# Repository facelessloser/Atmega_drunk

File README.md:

Atmega_drunk
============

Breathalyser build around the atmega328 with a OLED screen and a MQ-3 alcohol sensor

You will need the Adafruit OLED screen library. You can download them from here - https://github.com/adafruit/Adafruit_SSD1306

Also you will need the grafix library. You can download them from here - https://github.com/adafruit/Adafruit-GFX-Library

Blog post can be found here 

https://facelesstech.wordpress.com/2015/02/07/lets-get-atmega_drunk/

video can be found here

http://youtu.be/ZPd7yIUckZc

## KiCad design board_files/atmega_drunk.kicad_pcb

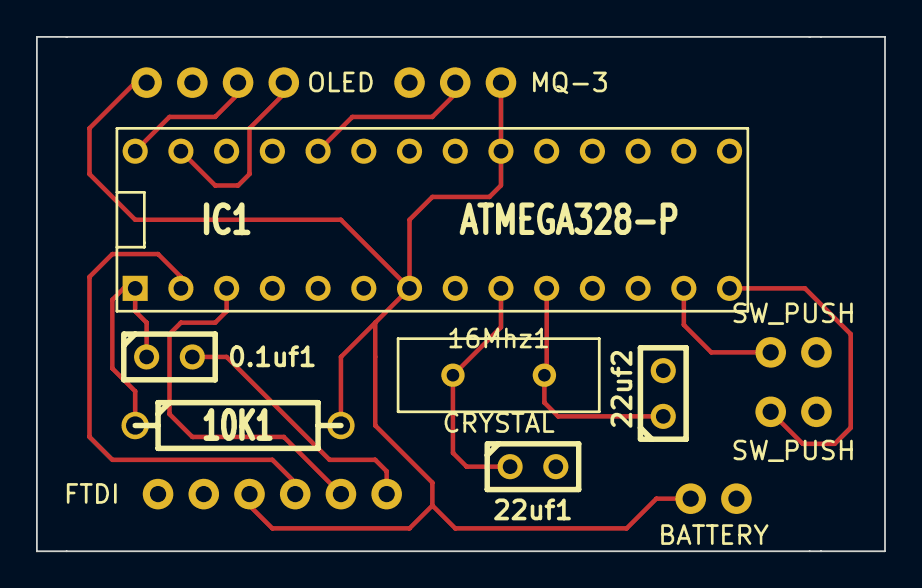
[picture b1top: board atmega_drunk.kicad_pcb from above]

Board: 2 copper layers, 47.1 x 28.6 mm, 13 parts (0 on the bottom side), 13 nets.

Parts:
0.1uf1, 22uf1, 22uf2: C; C1
10K1: R; R4-5
16Mhz1: CRYSTAL; Crystal_custom
BT1: BATTERY; Battery_headers
IC1: ATMEGA328-P; DIP_28_300_SOCKET
SW2: SW_PUSH; PUSH_BUTTONS_CUSTOM
U1: MQ-3
U2: FTDI
U3: OLED; OLED_HEADER
VAL: REF; OSH
eeSW3: SW_PUSH; PUSH_BUTTONS_CUSTOM

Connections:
GND: 22uf1.2, 22uf2.2, BT1.2, IC1.8, IC1.22, SW2.2, U1.1, U2.6, U3.2, eeSW3.2
unnamed: IC1.24, U1.2
unnamed: 0.1uf1.1, 10K1.1, IC1.1
unnamed: IC1.3, U2.2
unnamed: IC1.2, U2.3
unnamed: IC1.27, U3.4
unnamed: IC1.13, SW2.1
unnamed: IC1.14, eeSW3.1
unnamed: IC1.28, U3.3
unnamed: 16Mhz1.1, 22uf2.1, IC1.10
unnamed: 16Mhz1.2, 22uf1.1, IC1.9
unnamed: 0.1uf1.2, U2.1
VCC: 10K1.2, BT1.1, IC1.7, IC1.20, U1.3, U2.4, U3.1

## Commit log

2014-12-21 Gurber files to make atmega_drunk
2015-01-12 atmege drunk schematics and breakboard layout
2015-01-13 added links to the OLED librarys
2015-01-13 Arduino files
2015-01-31 changed the font to be bigger size
2015-02-01 changed font size and wrote centering code
2015-02-04 added phases to the drunk score
2015-02-04 removed commented code
2015-02-07 added video and blog post links
2015-02-15 fixed compiler errors
2015-02-15 changed name and fixed code
2015-02-15 changed name of dir
2015-02-15 rewrote atmega_drunk using MicroLCD library
2016-09-24 Board files for Atmega_drunk
2016-09-24 changed name
